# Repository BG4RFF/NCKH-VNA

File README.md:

# NCKH-VNA
Nghiên cứu khoa học 2017: Low-cost vector network analyzer – VNA for measuring the antenna of IoT devices.

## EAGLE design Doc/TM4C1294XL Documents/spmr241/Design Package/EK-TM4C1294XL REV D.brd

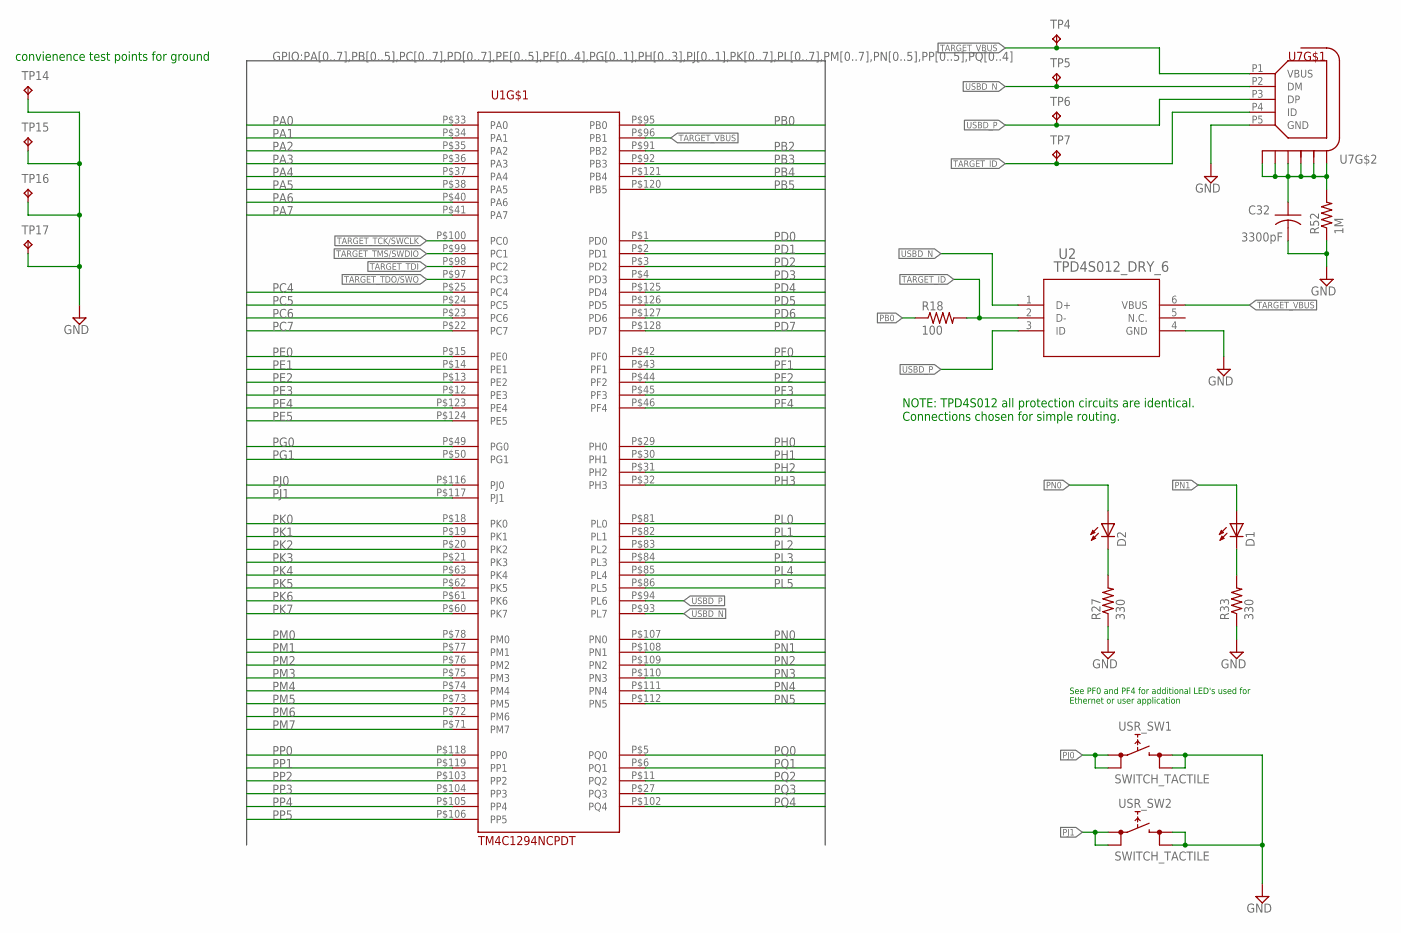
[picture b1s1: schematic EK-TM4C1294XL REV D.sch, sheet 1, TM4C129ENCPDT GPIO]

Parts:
C32: 3300pF; C0603
D1, D2: LEDCHIPLED_0603; CHIPLED_0603
R18: 100; R0402
R27, R33: 330; R0402
R52: 1M; R0603
TP4, TP5, TP6, TP7, TP14, TP15, TP16, TP17: TPPAD1-13; P1-13
U1: TM4C1294NCPDT; TQFP-128
U2: TPD4S012_DRY_6; DRY6
U7: CON_USB_HIROSE_MICRO_AB_ZX62D_AB_5P8; CON_USB_MICRO_AB_HIROSE_ZX62D-AB-5P8
USR_SW1, USR_SW2: SWITCH_TACTILE; SWITCH_6MM_6MM_TE_CON_SMD

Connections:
GND: C32.2, R27.1, R33.1, R52.1, TP14.TP, TP15.TP, TP16.TP, TP17.TP, U2.4 (GND), U7.P5 (GND), USR_SW1.P$3 (1), USR_SW1.P$4 (1), USR_SW2.P$3 (1), USR_SW2.P$4 (1); also elsewhere on the board
unnamed: D1.C, R33.2
unnamed: C32.1, R52.2, U7.P$1 (S1), U7.P$2 (S2), U7.P$3 (S3), U7.P$4 (S4), U7.P$5 (S5), U7.P$6 (S6)
unnamed: D2.C, R27.2
PA0: U1.P$33 (PA0); also elsewhere on the board
PA1: U1.P$34 (PA1); also elsewhere on the board
PA2: U1.P$35 (PA2); also elsewhere on the board
PA3: U1.P$36 (PA3); also elsewhere on the board
PA4: U1.P$37 (PA4); also elsewhere on the board
PA5: U1.P$38 (PA5); also elsewhere on the board
PA6: U1.P$40 (PA6); also elsewhere on the board
PA7: U1.P$41 (PA7); also elsewhere on the board
PB0: R18.1, U1.P$95 (PB0); also elsewhere on the board
PB2: U1.P$91 (PB2); also elsewhere on the board
PB3: U1.P$92 (PB3); also elsewhere on the board
PB4: U1.P$121 (PB4); also elsewhere on the board
PB5: U1.P$120 (PB5); also elsewhere on the board
PC4: U1.P$25 (PC4); also elsewhere on the board
PC5: U1.P$24 (PC5); also elsewhere on the board
PC6: U1.P$23 (PC6); also elsewhere on the board
PC7: U1.P$22 (PC7); also elsewhere on the board
PD0: U1.P$1 (PD0); also elsewhere on the board
PD1: U1.P$2 (PD1); also elsewhere on the board
PD2: U1.P$3 (PD2); also elsewhere on the board
PD3: U1.P$4 (PD3); also elsewhere on the board
PD4: U1.P$125 (PD4); also elsewhere on the board
PD5: U1.P$126 (PD5); also elsewhere on the board
PD6: U1.P$127 (PD6); also elsewhere on the board
PD7: U1.P$128 (PD7); also elsewhere on the board
PE0: U1.P$15 (PE0); also elsewhere on the board
PE1: U1.P$14 (PE1); also elsewhere on the board
PE2: U1.P$13 (PE2); also elsewhere on the board
PE3: U1.P$12 (PE3); also elsewhere on the board
PE4: U1.P$123 (PE4); also elsewhere on the board
PE5: U1.P$124 (PE5); also elsewhere on the board
PF0: U1.P$42 (PF0); also elsewhere on the board
PF1: U1.P$43 (PF1); also elsewhere on the board
PF2: U1.P$44 (PF2); also elsewhere on the board
PF3: U1.P$45 (PF3); also elsewhere on the board
PF4: U1.P$46 (PF4); also elsewhere on the board
PG0: U1.P$49 (PG0); also elsewhere on the board
PG1: U1.P$50 (PG1); also elsewhere on the board
PH0: U1.P$29 (PH0); also elsewhere on the board
PH1: U1.P$30 (PH1); also elsewhere on the board
PH2: U1.P$31 (PH2); also elsewhere on the board
PH3: U1.P$32 (PH3); also elsewhere on the board
PJ0: U1.P$116 (PJ0), USR_SW1.P$1 (0), USR_SW1.P$2 (0); also elsewhere on the board
PJ1: U1.P$117 (PJ1), USR_SW2.P$1 (0), USR_SW2.P$2 (0); also elsewhere on the board
PK0: U1.P$18 (PK0); also elsewhere on the board
PK1: U1.P$19 (PK1); also elsewhere on the board
PK2: U1.P$20 (PK2); also elsewhere on the board
PK3: U1.P$21 (PK3); also elsewhere on the board
PK4: U1.P$63 (PK4); also elsewhere on the board
PK5: U1.P$62 (PK5); also elsewhere on the board
PK6: U1.P$61 (PK6); also elsewhere on the board
PK7: U1.P$60 (PK7); also elsewhere on the board
PL0: U1.P$81 (PL0); also elsewhere on the board
PL1: U1.P$82 (PL1); also elsewhere on the board
PL2: U1.P$83 (PL2); also elsewhere on the board
PL3: U1.P$84 (PL3); also elsewhere on the board
PL4: U1.P$85 (PL4); also elsewhere on the board
PL5: U1.P$86 (PL5); also elsewhere on the board
PM0: U1.P$78 (PM0); also elsewhere on the board
PM1: U1.P$77 (PM1); also elsewhere on the board
PM2: U1.P$76 (PM2); also elsewhere on the board
PM3: U1.P$75 (PM3); also elsewhere on the board
PM4: U1.P$74 (PM4); also elsewhere on the board
PM5: U1.P$73 (PM5); also elsewhere on the board
PM6: U1.P$72 (PM6); also elsewhere on the board
PM7: U1.P$71 (PM7); also elsewhere on the board
PN0: D2.A, U1.P$107 (PN0); also elsewhere on the board
PN1: D1.A, U1.P$108 (PN1); also elsewhere on the board
PN2: U1.P$109 (PN2); also elsewhere on the board
PN3: U1.P$110 (PN3); also elsewhere on the board
PN4: U1.P$111 (PN4); also elsewhere on the board
PN5: U1.P$112 (PN5); also elsewhere on the board
PP0: U1.P$118 (PP0); also elsewhere on the board
PP1: U1.P$119 (PP1); also elsewhere on the board
PP2: U1.P$103 (PP2); also elsewhere on the board
PP3: U1.P$104 (PP3); also elsewhere on the board
PP4: U1.P$105 (PP4); also elsewhere on the board
PP5: U1.P$106 (PP5); also elsewhere on the board
PQ0: U1.P$5 (PQ0); also elsewhere on the board
PQ1: U1.P$6 (PQ1); also elsewhere on the board
PQ2: U1.P$11 (PQ2); also elsewhere on the board
PQ3: U1.P$27 (PQ3); also elsewhere on the board
PQ4: U1.P$102 (PQ4); also elsewhere on the board
TARGET_ID: R18.2, TP7.TP, U2.2 (D-), U7.P4 (ID)
TARGET_TCK/SWCLK: U1.P$100 (PC0); also elsewhere on the board
TARGET_TDI: U1.P$98 (PC2); also elsewhere on the board
TARGET_TDO/SWO: U1.P$97 (PC3); also elsewhere on the board
TARGET_TMS/SWDIO: U1.P$99 (PC1); also elsewhere on the board
TARGET_VBUS: TP4.TP, U1.P$96 (PB1), U2.6 (VBUS), U7.P1 (VBUS); also elsewhere on the board
USBD_N: TP5.TP, U1.P$93 (PL7), U2.1 (D+), U7.P2 (DM)
USBD_P: TP6.TP, U1.P$94 (PL6), U2.3 (ID), U7.P3 (DP)

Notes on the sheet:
See PF0 and PF4 for additional LED's used for Ethernet or user application
NOTE: TPD4S012 all protection circuits are identical. Connections chosen for simple routing.
convienence test points for ground

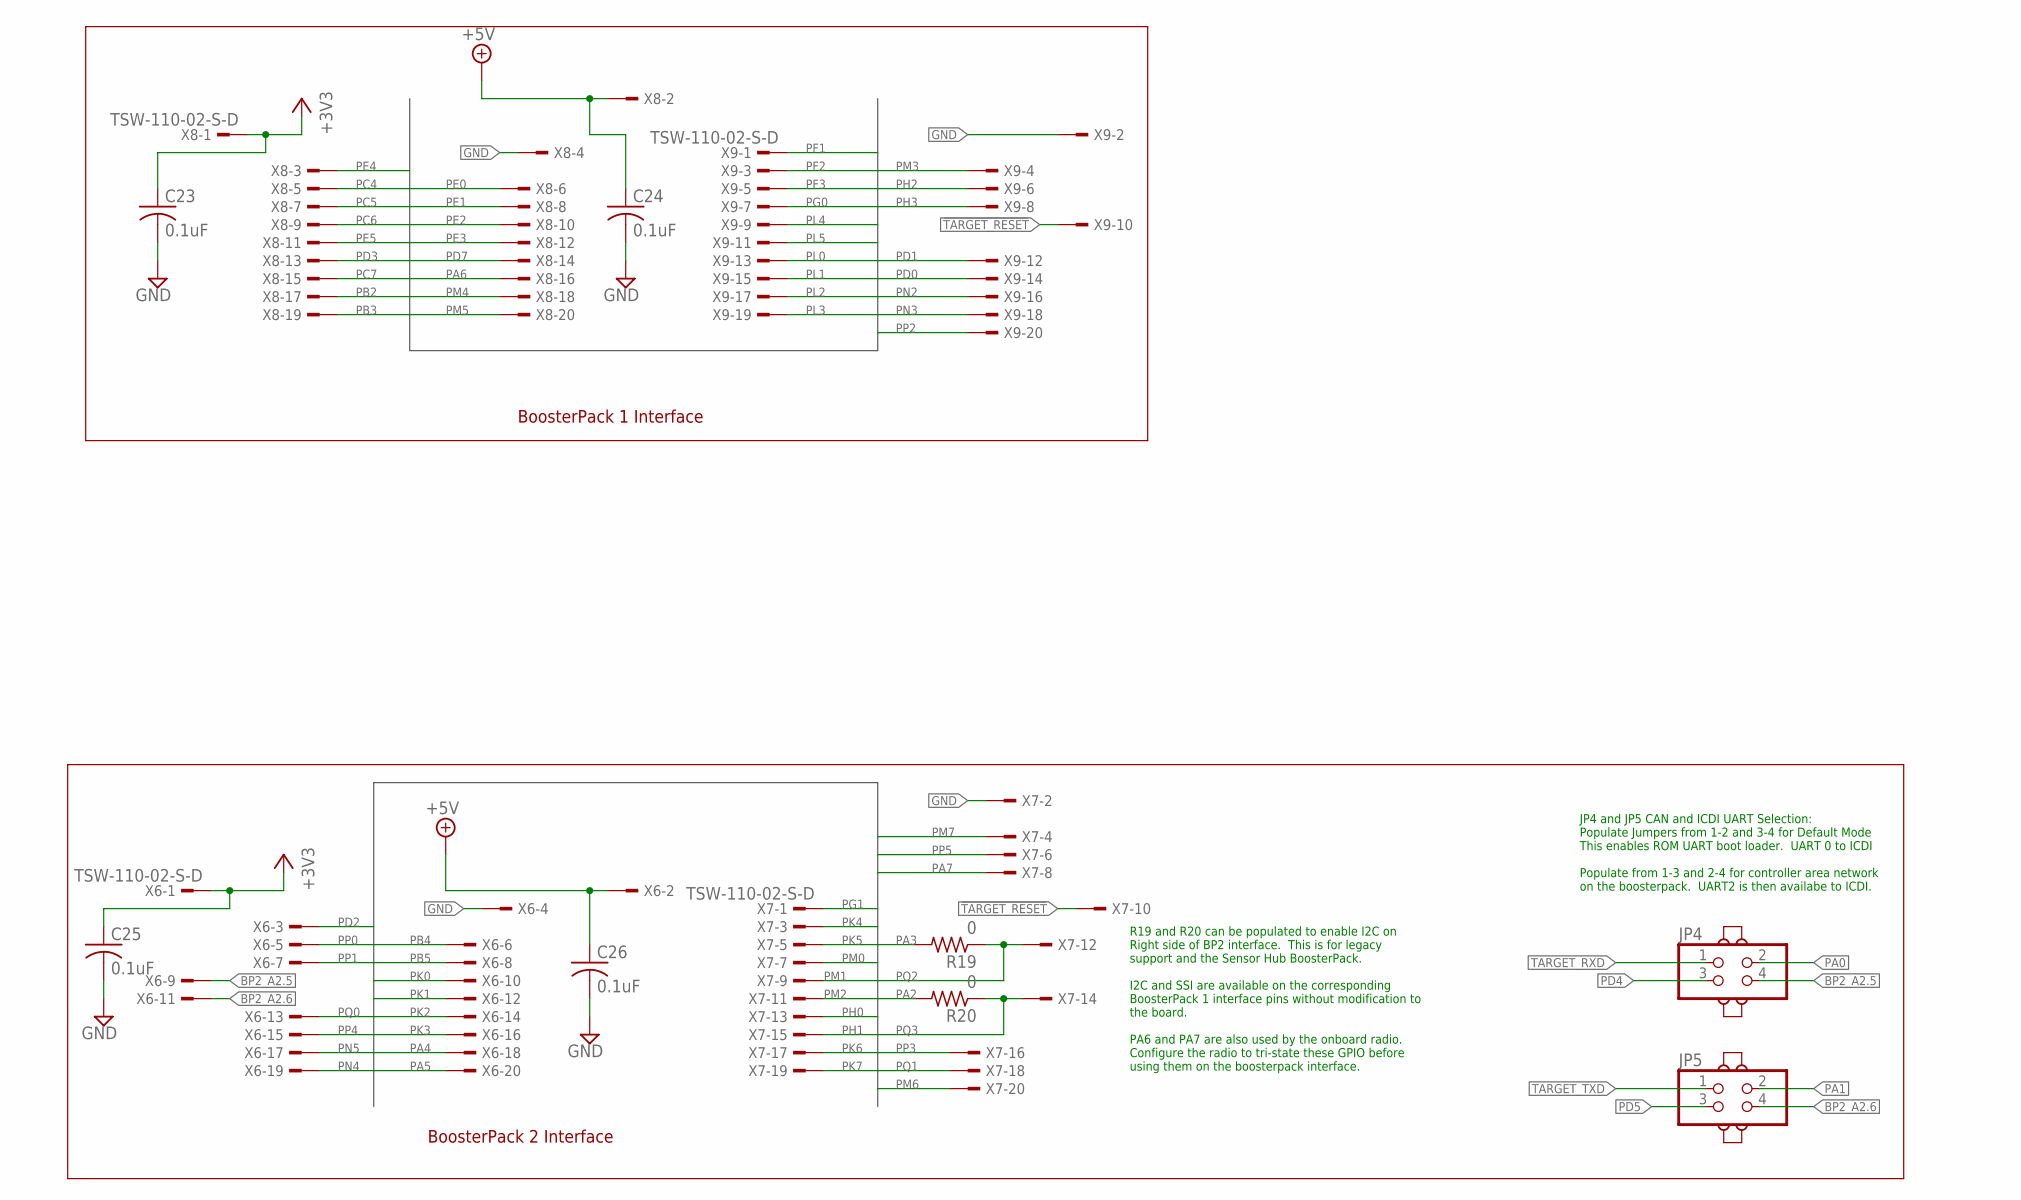
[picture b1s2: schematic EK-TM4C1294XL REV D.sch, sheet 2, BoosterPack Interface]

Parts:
C23, C24, C25, C26: 0.1uF; C0402
J4, J5, J6, J7: JUMPER; JUMP
JP4, JP5: PINHD-2X2; 2X02
R19, R20: 0; R0402
X6, X7, X8, X9: TSW-110-02-S-D

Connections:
!TARGET_RESET: X7.10, X9.10; also elsewhere on the board
+3V3: C23.1, C25.1, X6.1, X8.1; also elsewhere on the board
+5V: C24.1, C26.1, X6.2, X8.2; also elsewhere on the board
BP2_A2.5: JP4.4, X6.9
BP2_A2.6: JP5.4, X6.11
GND: C23.2, C24.2, C25.2, C26.2, X6.4, X7.2, X8.4, X9.2; also elsewhere on the board
PA0: JP4.2; also elsewhere on the board
PA1: JP5.2; also elsewhere on the board
PA2: R20.2; also elsewhere on the board
PA3: R19.2; also elsewhere on the board
PA4: X6.18; also elsewhere on the board
PA5: X6.20; also elsewhere on the board
PA6: X8.16; also elsewhere on the board
PA7: X7.8; also elsewhere on the board
PB2: X8.17; also elsewhere on the board
PB3: X8.19; also elsewhere on the board
PB4: X6.6; also elsewhere on the board
PB5: X6.8; also elsewhere on the board
PC4: X8.5; also elsewhere on the board
PC5: X8.7; also elsewhere on the board
PC6: X8.9; also elsewhere on the board
PC7: X8.15; also elsewhere on the board
PD0: X9.14; also elsewhere on the board
PD1: X9.12; also elsewhere on the board
PD2: X6.3; also elsewhere on the board
PD3: X8.13; also elsewhere on the board
PD4: JP4.3; also elsewhere on the board
PD5: JP5.3; also elsewhere on the board
PD7: X8.14; also elsewhere on the board
PE0: X8.6; also elsewhere on the board
PE1: X8.8; also elsewhere on the board
PE2: X8.10; also elsewhere on the board
PE3: X8.12; also elsewhere on the board
PE4: X8.3; also elsewhere on the board
PE5: X8.11; also elsewhere on the board
PF1: X9.1; also elsewhere on the board
PF2: X9.3; also elsewhere on the board
PF3: X9.5; also elsewhere on the board
PG0: X9.7; also elsewhere on the board
PG1: X7.1; also elsewhere on the board
PH0: X7.13; also elsewhere on the board
PH1: X7.15; also elsewhere on the board
PH2: X9.6; also elsewhere on the board
PH3: X9.8; also elsewhere on the board
PK0: X6.10; also elsewhere on the board
PK1: X6.12; also elsewhere on the board
PK2: X6.14; also elsewhere on the board
PK3: X6.16; also elsewhere on the board
PK4: X7.3; also elsewhere on the board
PK5: X7.5; also elsewhere on the board
PK6: X7.17; also elsewhere on the board
PK7: X7.19; also elsewhere on the board
PL0: X9.13; also elsewhere on the board
PL1: X9.15; also elsewhere on the board
PL2: X9.17; also elsewhere on the board
PL3: X9.19; also elsewhere on the board
PL4: X9.9; also elsewhere on the board
PL5: X9.11; also elsewhere on the board
PM0: X7.7; also elsewhere on the board
PM1: X7.9; also elsewhere on the board
PM2: X7.11; also elsewhere on the board
PM3: X9.4; also elsewhere on the board
PM4: X8.18; also elsewhere on the board
PM5: X8.20; also elsewhere on the board
PM6: X7.20; also elsewhere on the board
PM7: X7.4; also elsewhere on the board
PN2: X9.16; also elsewhere on the board
PN3: X9.18; also elsewhere on the board
PN4: X6.19; also elsewhere on the board
PN5: X6.17; also elsewhere on the board
PP0: X6.5; also elsewhere on the board
PP1: X6.7; also elsewhere on the board
PP2: X9.20; also elsewhere on the board
PP3: X7.16; also elsewhere on the board
PP4: X6.15; also elsewhere on the board
PP5: X7.6; also elsewhere on the board
PQ0: X6.13; also elsewhere on the board
PQ1: X7.18; also elsewhere on the board
PQ2: R19.1, X7.12; also elsewhere on the board
PQ3: R20.1, X7.14; also elsewhere on the board
TARGET_RXD: JP4.1; also elsewhere on the board
TARGET_TXD: JP5.1; also elsewhere on the board

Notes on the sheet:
BoosterPack 2 Interface
BoosterPack 1 Interface
JP4 and JP5 CAN and ICDI UART Selection: Populate Jumpers from 1-2 and 3-4 for Default Mode This enables ROM UART boot loader. UART 0 to ICDI Populate from 1-3 and 2-4 for controller area network on the boosterpack. UART2 is then availabe to ICDI.
R19 and R20 can be populated to enable I2C on Right side of BP2 interface. This is for legacy support and the Sensor Hub BoosterPack. I2C and SSI are available on the corresponding BoosterPack 1 interface pins without modification to the board. PA6 and PA7 are also used by the onboard radio. Config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

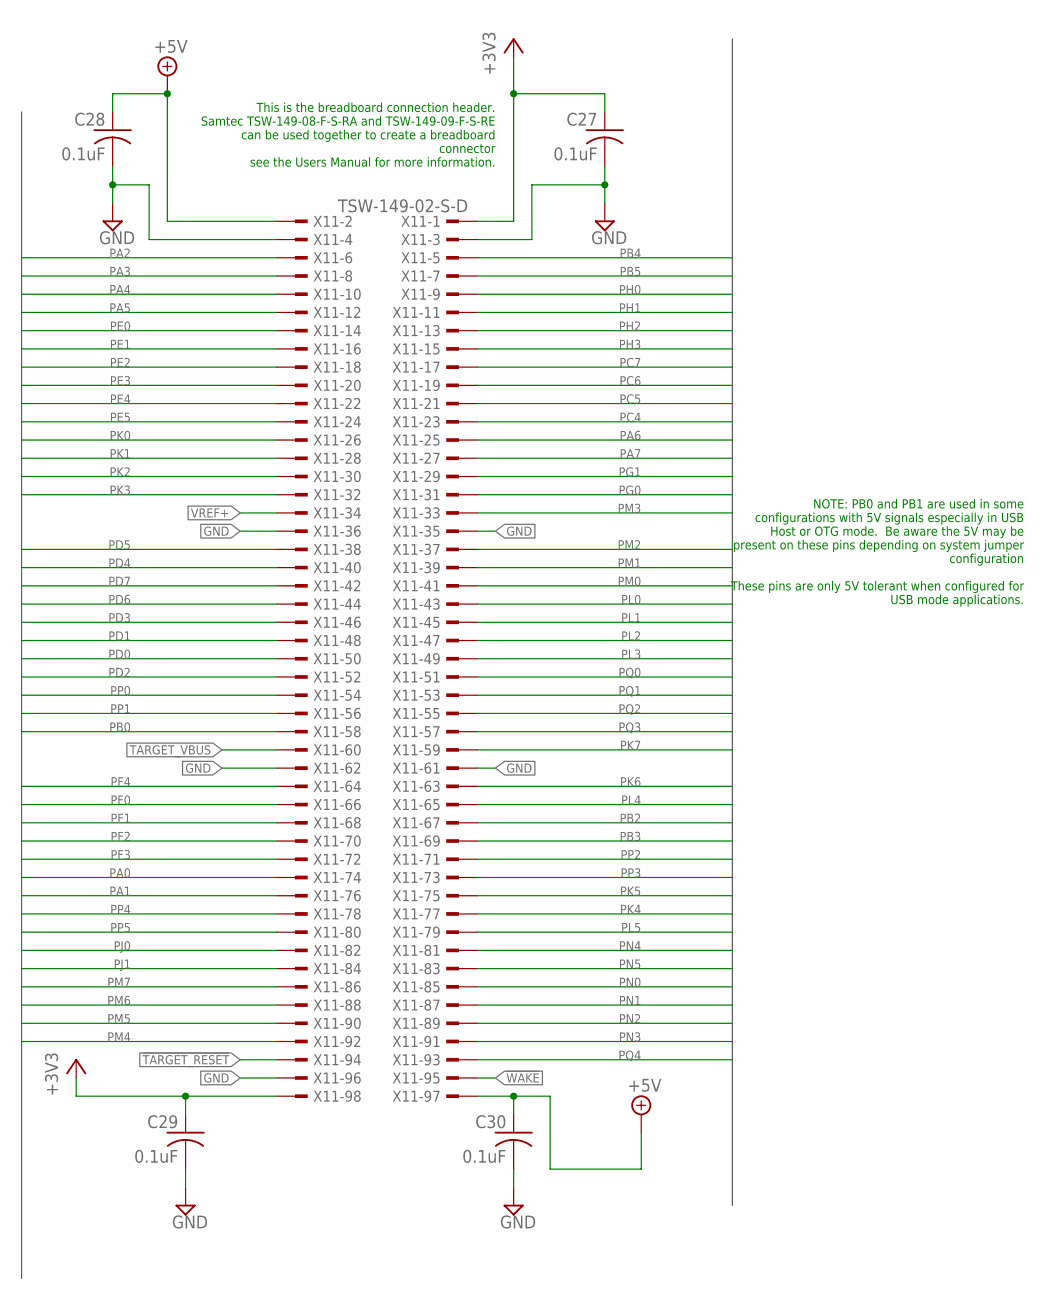
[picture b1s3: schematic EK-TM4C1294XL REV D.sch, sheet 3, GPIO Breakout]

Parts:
C27, C28, C29, C30: 0.1uF; C0402
X11: TSW-149-02-S-D

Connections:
!TARGET_RESET: X11.94; also elsewhere on the board
!WAKE: X11.95; also elsewhere on the board
+3V3: C27.1, C29.1, X11.1, X11.98; also elsewhere on the board
+5V: C28.1, C30.1, X11.2, X11.97; also elsewhere on the board
GND: C27.2, C28.2, C29.2, C30.2, X11.3, X11.4, X11.35, X11.36, X11.61, X11.62, X11.96; also elsewhere on the board
PA0: X11.74; also elsewhere on the board
PA1: X11.76; also elsewhere on the board
PA2: X11.6; also elsewhere on the board
PA3: X11.8; also elsewhere on the board
PA4: X11.10; also elsewhere on the board
PA5: X11.12; also elsewhere on the board
PA6: X11.25; also elsewhere on the board
PA7: X11.27; also elsewhere on the board
PB0: X11.58; also elsewhere on the board
PB2: X11.67; also elsewhere on the board
PB3: X11.69; also elsewhere on the board
PB4: X11.5; also elsewhere on the board
PB5: X11.7; also elsewhere on the board
PC4: X11.23; also elsewhere on the board
PC5: X11.21; also elsewhere on the board
PC6: X11.19; also elsewhere on the board
PC7: X11.17; also elsewhere on the board
PD0: X11.50; also elsewhere on the board
PD1: X11.48; also elsewhere on the board
PD2: X11.52; also elsewhere on the board
PD3: X11.46; also elsewhere on the board
PD4: X11.40; also elsewhere on the board
PD5: X11.38; also elsewhere on the board
PD6: X11.44; also elsewhere on the board
PD7: X11.42; also elsewhere on the board
PE0: X11.14; also elsewhere on the board
PE1: X11.16; also elsewhere on the board
PE2: X11.18; also elsewhere on the board
PE3: X11.20; also elsewhere on the board
PE4: X11.22; also elsewhere on the board
PE5: X11.24; also elsewhere on the board
PF0: X11.66; also elsewhere on the board
PF1: X11.68; also elsewhere on the board
PF2: X11.70; also elsewhere on the board
PF3: X11.72; also elsewhere on the board
PF4: X11.64; also elsewhere on the board
PG0: X11.31; also elsewhere on the board
PG1: X11.29; also elsewhere on the board
PH0: X11.9; also elsewhere on the board
PH1: X11.11; also elsewhere on the board
PH2: X11.13; also elsewhere on the board
PH3: X11.15; also elsewhere on the board
PJ0: X11.82; also elsewhere on the board
PJ1: X11.84; also elsewhere on the board
PK0: X11.26; also elsewhere on the board
PK1: X11.28; also elsewhere on the board
PK2: X11.30; also elsewhere on the board
PK3: X11.32; also elsewhere on the board
PK4: X11.77; also elsewhere on the board
PK5: X11.75; also elsewhere on the board
PK6: X11.63; also elsewhere on the board
PK7: X11.59; also elsewhere on the board
PL0: X11.43; also elsewhere on the board
PL1: X11.45; also elsewhere on the board
PL2: X11.47; also elsewhere on the board
PL3: X11.49; also elsewhere on the board
PL4: X11.65; also elsewhere on the board
PL5: X11.79; also elsewhere on the board
PM0: X11.41; also elsewhere on the board
PM1: X11.39; also elsewhere on the board
PM2: X11.37; also elsewhere on the board
PM3: X11.33; also elsewhere on the board
PM4: X11.92; also elsewhere on the board
PM5: X11.90; also elsewhere on the board
PM6: X11.88; also elsewhere on the board
PM7: X11.86; also elsewhere on the board
PN0: X11.85; also elsewhere on the board
PN1: X11.87; also elsewhere on the board
PN2: X11.89; also elsewhere on the board
PN3: X11.91; also elsewhere on the board
PN4: X11.81; also elsewhere on the board
PN5: X11.83; also elsewhere on the board
PP0: X11.54; also elsewhere on the board
PP1: X11.56; also elsewhere on the board
PP2: X11.71; also elsewhere on the board
PP3: X11.73; also elsewhere on the board
PP4: X11.78; also elsewhere on the board
PP5: X11.80; also elsewhere on the board
PQ0: X11.51; also elsewhere on the board
PQ1: X11.53; also elsewhere on the board
PQ2: X11.55; also elsewhere on the board
PQ3: X11.57; also elsewhere on the board
PQ4: X11.93; also elsewhere on the board
TARGET_VBUS: X11.60; also elsewhere on the board
VREF+: X11.34; also elsewhere on the board

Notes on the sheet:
NOTE: PB0 and PB1 are used in some configurations with 5V signals especially in USB Host or OTG mode. Be aware the 5V may be present on these pins depending on system jumper configuration These pins are only 5V tolerant when configured for USB mode applications.
This is the breadboard connection header. Samtec TSW-149-08-F-S-RA and TSW-149-09-F-S-RE can be used together to create a breadboard connector see the Users Manual for more information.

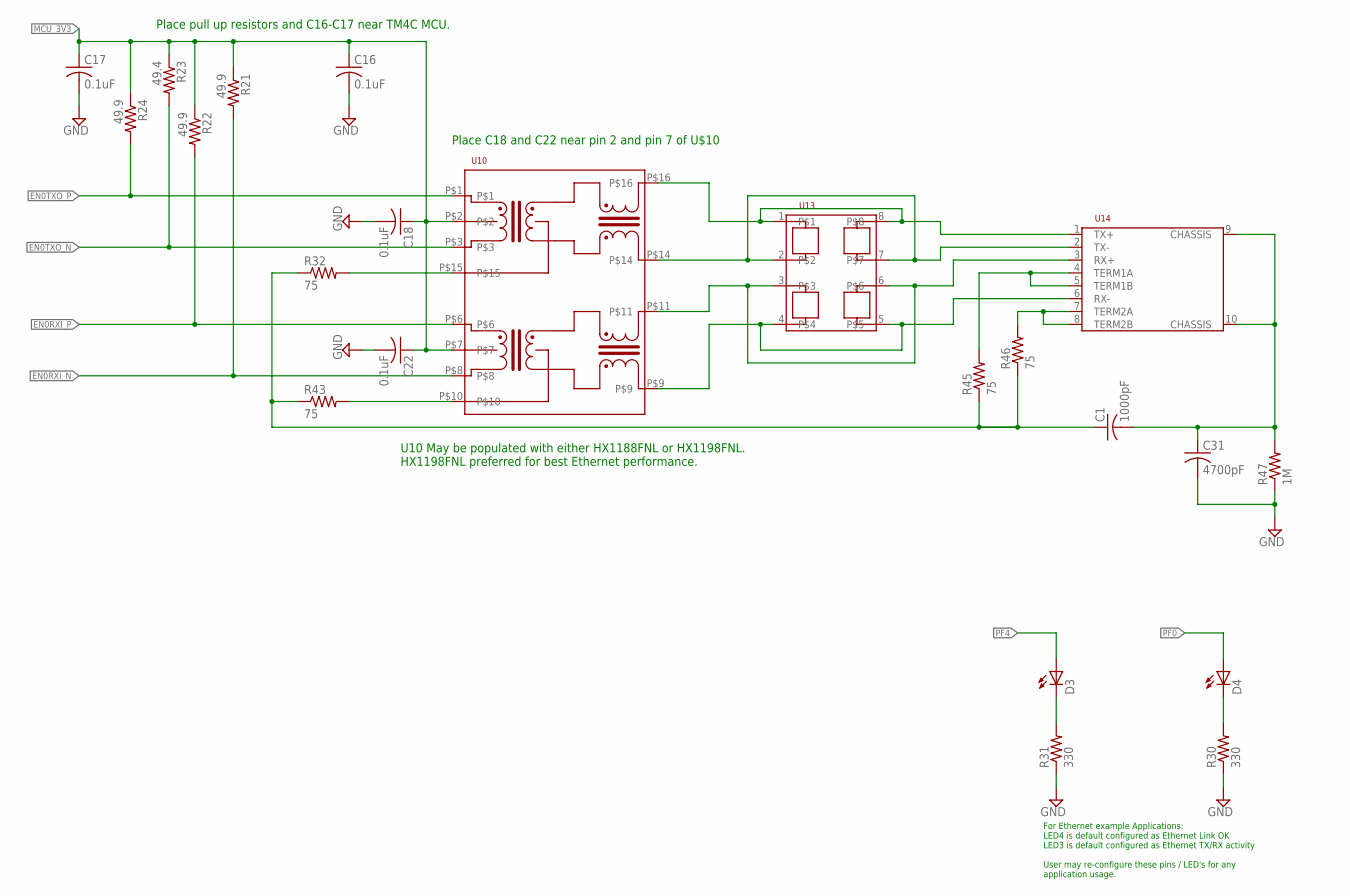
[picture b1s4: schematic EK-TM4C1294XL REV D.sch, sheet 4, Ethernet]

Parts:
C1: 1000pF; C1210
C16, C17, C18, C22: 0.1uF; C0402
C31: 4700pF; C1812
D3, D4: LEDCHIPLED_0603; CHIPLED_0603
R21, R22, R24: 49.9; R0402
R23: 49.4; R0402
R30, R31: 330; R0402
R32, R43, R45, R46: 75; R0402
R47: 1M; R1206
U10: MAG_PULSE_HX1188FNL
U13: SLVU2.8-4; D8
U14: JACK_RJ45_NOMAG_NOLED_TECON; RJ45_TE_CON_NOMAG_NOLED

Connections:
CHASSIS: C1.2, C31.1, R47.2, U14.9 (CHASSIS), U14.10 (CHASSIS)
EN0RXI_N: R21.2, U10.P$8; also elsewhere on the board
EN0RXI_P: R22.2, U10.P$6; also elsewhere on the board
EN0TXO_N: R23.2, U10.P$3; also elsewhere on the board
EN0TXO_P: R24.2, U10.P$1; also elsewhere on the board
GND: C16.2, C17.2, C18.2, C22.2, C31.2, R30.1, R31.1, R47.1; also elsewhere on the board
JACK_RX_N: U10.P$9, U13.4, U13.5, U14.6 (RX-)
JACK_RX_P: U10.P$11, U13.3, U13.6, U14.3 (RX+)
JACK_TX_N: U10.P$14, U13.2, U13.7, U14.2 (TX-)
JACK_TX_P: U10.P$16, U13.1, U13.8, U14.1 (TX+)
MCU_3V3: C16.1, C17.1, C18.1, C22.1, R21.1, R22.1, R23.1, R24.1, U10.P$2, U10.P$7; also elsewhere on the board
unnamed: D4.C, R30.2
unnamed: D3.C, R31.2
unnamed: R32.2, U10.P$15
unnamed: R43.2, U10.P$10
unnamed: C1.1, R32.1, R43.1, R45.1, R46.1
unnamed: R45.2, U14.4 (TERM1A), U14.5 (TERM1B)
unnamed: R46.2, U14.7 (TERM2A), U14.8 (TERM2B)
PF0: D4.A; also elsewhere on the board
PF4: D3.A; also elsewhere on the board

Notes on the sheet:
For Ethernet example Applications: LED4 is default configured as Ethernet Link OK LED3 is default configured as Ethernet TX/RX activity User may re-configure these pins / LED's for any application usage.
Place pull up resistors and C16-C17 near TM4C MCU.
Place C18 and C22 near pin 2 and pin 7 of U$10
U10 May be populated with either HX1188FNL or HX1198FNL. HX1198FNL preferred for best Ethernet performance.

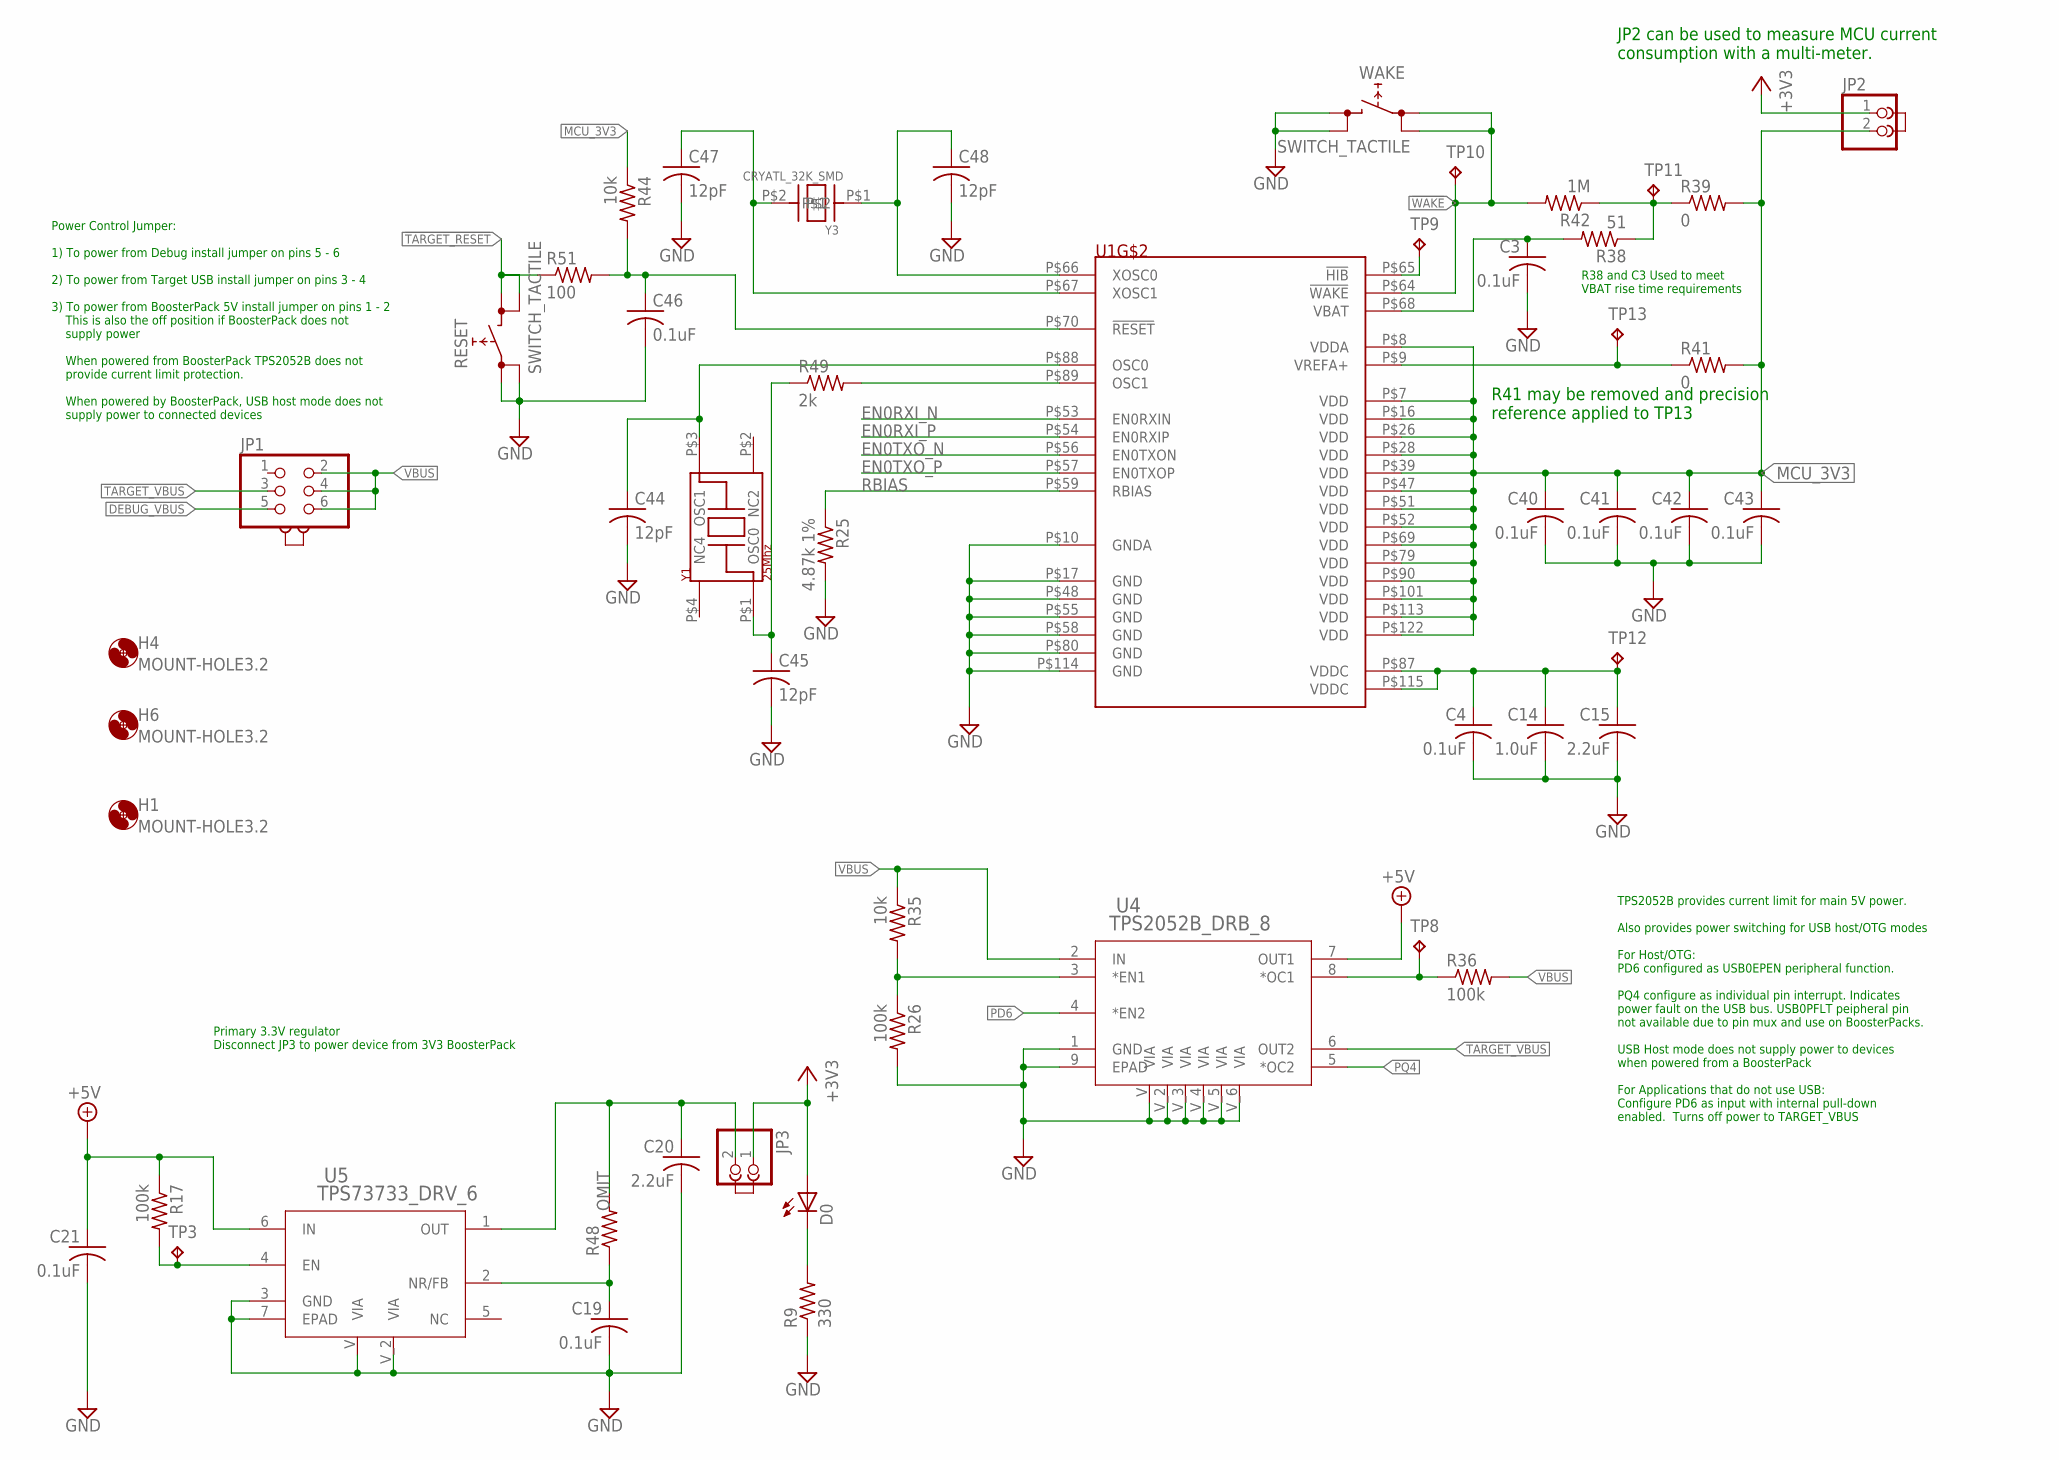
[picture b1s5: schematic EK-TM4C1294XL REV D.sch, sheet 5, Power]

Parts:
C3, C4, C19, C21, C40, C41, C42, C43, C46: 0.1uF; C0402
C14: 1.0uF; C0402
C15, C20: 2.2uF; C0603K; DIGIKEY_PARTNUM 311-1451-2-ND
C44, C45, C47, C48: 12pF; C0402
D0: LEDCHIPLED_0603; CHIPLED_0603
H1, H4, H6: MOUNT-HOLE3.2; 3,2
J1, J2, J3: JUMPER; JUMP
JP1: PINHD-2X3; 2X03
JP2, JP3: PINHD-1X2; 1X02
R9: 330; R0402
R17, R26, R36: 100k; R0402
R25: 4.87k 1%; R0402
R35, R44: 10k; R0402
R38: 51; R0402
R39, R41: 0; R0402
R42: 1M; R0402
R48: R-US_R0402; R0402
R49: 2k; R0402
R51: 100; R0402
RESET: SWITCH_TACTILE; SWITCH_6MM_6MM_TE_CON_SMD
TP3, TP8, TP9, TP10, TP11, TP12, TP13: TPPAD1-13; P1-13
U1: TM4C1294NCPDT; TQFP-128
U4: TPS2052B_DRB_8; DRB8_2P4X1P65
U5: TPS73733_DRV_6; DRV6_1P6X1
WAKE: SWITCH_TACTILE; SWITCH_6MM_6MM_TE_CON_SMD
Y1: 25Mhz; NDK3.2X2.5
Y3: CRYATL_32K_SMD; CRYSTAL_32K_SMD

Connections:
!HIB: TP9.TP, U1.P$65 (!HIB)
!TARGET_RESET: R51.1, RESET.P$3 (1), RESET.P$4 (1); also elsewhere on the board
!TARGET_RESET_FILTERED: C46.1, R44.2, R51.2, U1.P$70 (!RESET)
!WAKE: R42.2, TP10.TP, U1.P$64 (!WAKE), WAKE.P$1 (0), WAKE.P$2 (0); also elsewhere on the board
+3V3: D0.A, JP2.1, JP3.1; also elsewhere on the board
+5V: C21.1, R17.1, U4.7 (OUT1), U5.6 (IN); also elsewhere on the board
DEBUG_VBUS: JP1.5; also elsewhere on the board
EN0RXI_N: U1.P$53 (EN0RXIN); also elsewhere on the board
EN0RXI_P: U1.P$54 (EN0RXIP); also elsewhere on the board
EN0TXO_N: U1.P$56 (EN0TXON); also elsewhere on the board
EN0TXO_P: U1.P$57 (EN0TXOP); also elsewhere on the board
GND: C3.2, C4.2, C14.2, C15.2, C19.2, C20.2, C21.2, C40.2, C41.2, C42.2, C43.2, C44.2, C45.2, C46.2, C47.2, C48.2, R9.1, R25.2, R26.2, RESET.P$1 (0), RESET.P$2 (0), U1.P$10 (GNDA), U1.P$17 (GND), U1.P$48 (GND), U1.P$55 (GND), U1.P$58 (GND), U1.P$80 (GND), U1.P$114 (GND), U4.1 (GND), U4.9 (EPAD), U4.V (VIA), U4.V_2 (VIA), U4.V_3 (VIA), U4.V_4 (VIA), U4.V_5 (VIA), U4.V_6 (VIA), U5.3 (GND), U5.7 (EPAD), U5.V (VIA), U5.V_2 (VIA), WAKE.P$3 (1), WAKE.P$4 (1); also elsewhere on the board
MCU_3V3: C40.1, C41.1, C42.1, C43.1, JP2.2, R39.2, R41.2, R44.1, U1.P$7 (VDD), U1.P$8 (VDDA), U1.P$16 (VDD), U1.P$26 (VDD), U1.P$28 (VDD), U1.P$39 (VDD), U1.P$47 (VDD), U1.P$51 (VDD), U1.P$52 (VDD), U1.P$69 (VDD), U1.P$79 (VDD), U1.P$90 (VDD), U1.P$101 (VDD), U1.P$113 (VDD), U1.P$122 (VDD); also elsewhere on the board
unnamed: D0.C, R9.2
unnamed: R26.1, R35.2, U4.3 (*EN1)
unnamed: C19.1, R48.1, U5.2 (NR/FB)
unnamed: R36.1, TP8.TP, U4.8 (*OC1)
unnamed: C3.1, R38.2, U1.P$68 (VBAT)
unnamed: C20.1, JP3.2, R48.2, U5.1 (OUT)
unnamed: R49.2, U1.P$89 (OSC1)
unnamed: C45.1, R49.1, Y1.P$1 (OSC0)
unnamed: C47.1, U1.P$67 (XOSC1), Y3.P$2
unnamed: C44.1, U1.P$88 (OSC0), Y1.P$3 (OSC1)
unnamed: C48.1, U1.P$66 (XOSC0), Y3.P$1
PD6: U4.4 (*EN2); also elsewhere on the board
PQ4: U4.5 (*OC2); also elsewhere on the board
RBIAS: R25.1, U1.P$59 (RBIAS)
TARGET_VBUS: JP1.3, U4.6 (OUT2); also elsewhere on the board
TARGET_VDDC: C4.1, C14.1, C15.1, TP12.TP, U1.P$87 (VDDC), U1.P$115 (VDDC)
VBAT: R38.1, R39.1, R42.1, TP11.TP
VBUS: JP1.2, JP1.4, JP1.6, R35.1, R36.2, U4.2 (IN)
VREF+: R41.1, TP13.TP, U1.P$9 (VREFA+); also elsewhere on the board
VREG_EN: R17.2, TP3.TP, U5.4 (EN)

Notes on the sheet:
Power Control Jumper: 1) To power from Debug install jumper on pins 5 - 6 2) To power from Target USB install jumper on pins 3 - 4 3) To power from BoosterPack 5V install jumper on pins 1 - 2 This is also the off position if BoosterPack does not supply power When powered from BoosterPack TPS2052B d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
Primary 3.3V regulator Disconnect JP3 to power device from 3V3 BoosterPack
JP2 can be used to measure MCU current consumption with a multi-meter.
TPS2052B provides current limit for main 5V power. Also provides power switching for USB host/OTG modes For Host/OTG: PD6 configured as USB0EPEN peripheral function. PQ4 configure as individual pin interrupt. Indicates power fault on the USB bus. USB0PFLT peipheral pin not available due to pin mux 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
R38 and C3 Used to meet VBAT rise time requirements
R41 may be removed and precision reference applied to TP13

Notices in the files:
parts and their libraries:
ek-tm4c129exl: ©2009 ROFA.cz
